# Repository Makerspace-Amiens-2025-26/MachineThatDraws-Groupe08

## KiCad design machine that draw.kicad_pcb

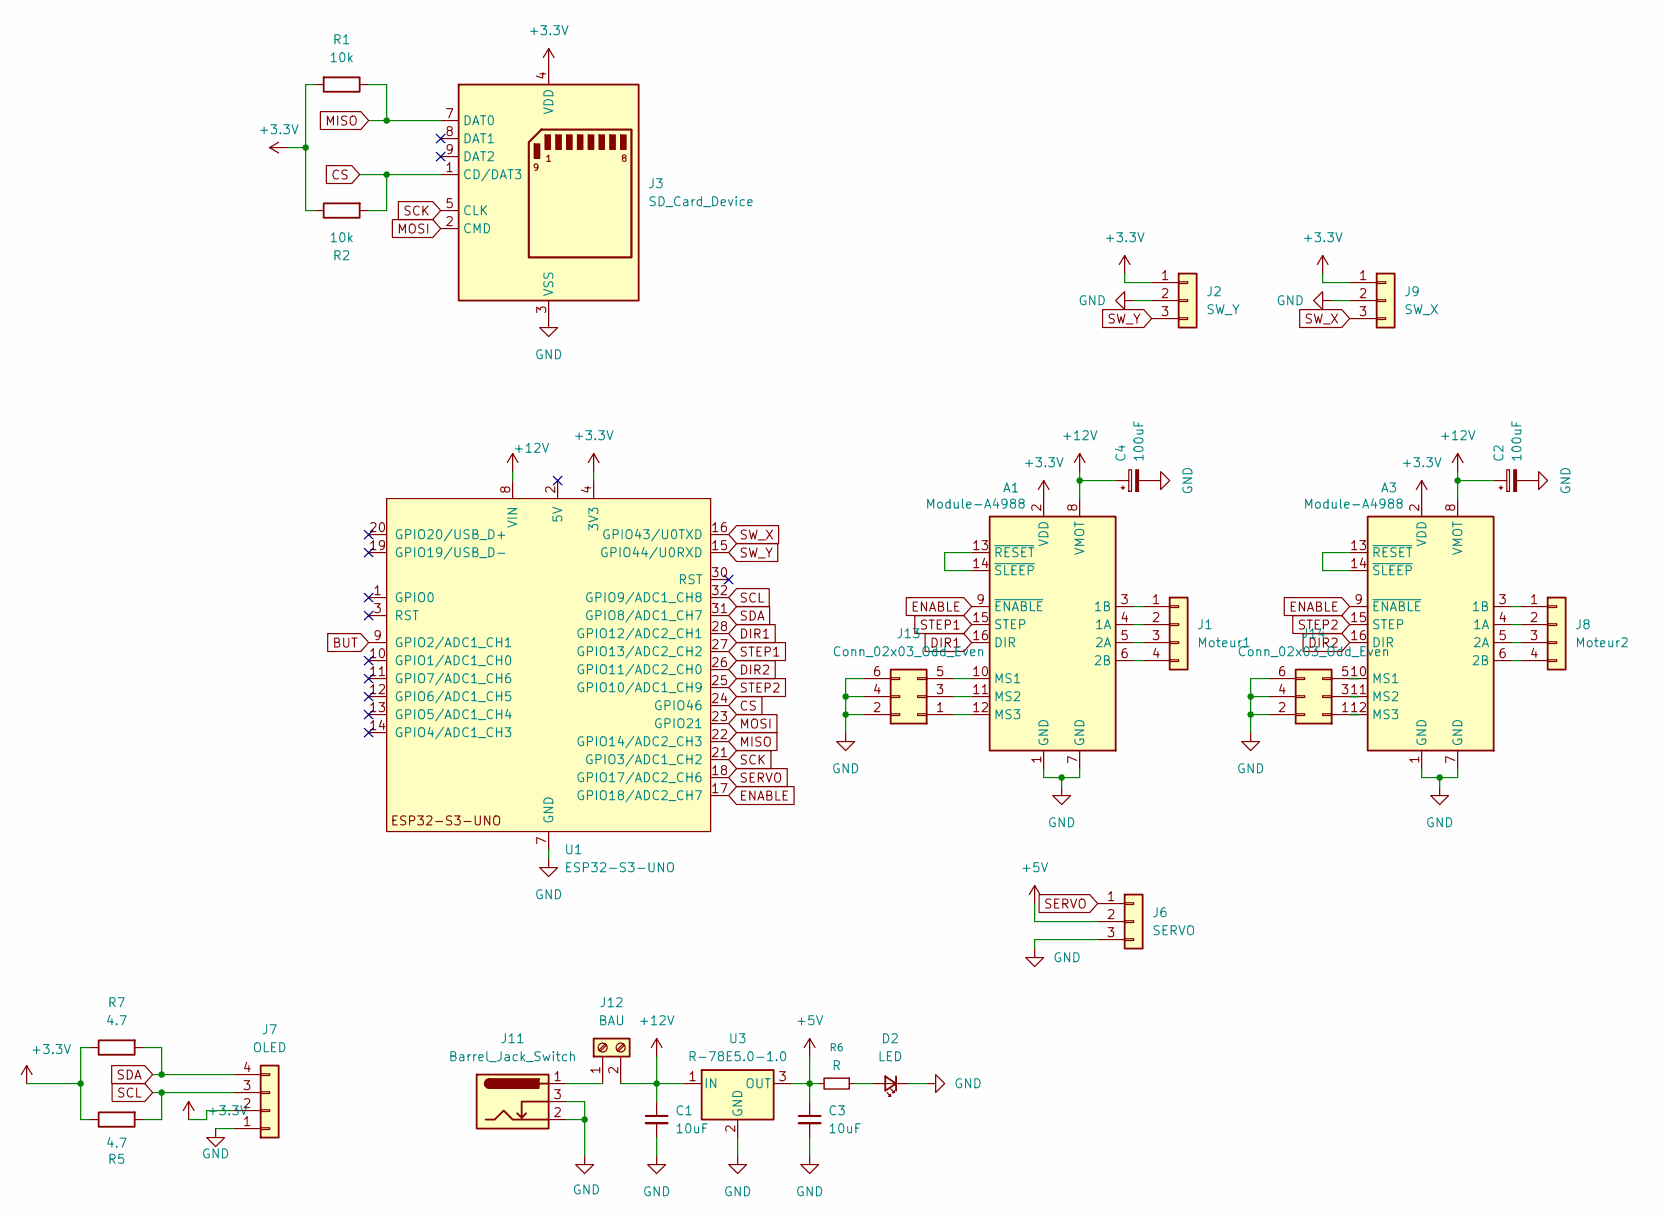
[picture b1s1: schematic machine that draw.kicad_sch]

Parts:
A1, A3: Module-A4988; Pololu_Breakout-16_15.2x20.3mm
C1, C3: 10uF; C_1206_3216Metric_Pad1.33x1.80mm_HandSolder
C2, C4: 100uF; CP_Radial_D8.0mm_P3.50mm
D2: LED; LED_1206_3216Metric_Pad1.42x1.75mm_HandSolder
J1: Moteur1; PinHeader_1x04_P2.54mm_Vertical
J2: SW_Y; PinHeader_1x03_P2.54mm_Vertical
J3: SD_Card_Device; SD_Hirose_DM1AA_SF_PEJ82
J6: SERVO; PinHeader_1x03_P2.54mm_Vertical
J7: OLED; PinHeader_1x04_P2.54mm_Vertical
J8: Moteur2; PinHeader_1x04_P2.54mm_Vertical
J9: SW_X; PinHeader_1x03_P2.54mm_Vertical
J11: Barrel_Jack_Switch; BarrelJack_Horizontal
J12: BAU; TerminalBlock_Phoenix_PT-1,5-2-5.0-H_1x02_P5.00mm_Horizontal
J13, J14: Conn_02x03_Odd_Even; PinHeader_2x03_P2.54mm_Vertical
R1, R2: 10k; R_1206
R5, R7: 4.7; R_1206
R6: R; R_1206
U1: ESP32-S3-UNO; ESP_S3_UNO
U3: R-78E5.0-1.0; Converter_DCDC_RECOM_R-78E-0.5_THT

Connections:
+3.3V: A1.2 (VDD), A3.2 (VDD), J2.1, J3.4 (VDD), J7.2, J9.1, R1.2, R2.1, R5.1, R7.1, U1.4 (3V3)
+5V: C3.1, J6.2, R6.2, U3.3 (OUT)
+12V: A1.8 (VMOT), A3.8 (VMOT), C1.1, C2.1, C4.1, J12.2, U1.8 (VIN), U3.1 (IN)
BUT: U1.9 (GPIO2/ADC1_CH1)
CS: J3.1 (CD/DAT3), R2.2, U1.24 (GPIO46)
DIR1: A1.16 (DIR), U1.28 (GPIO12/ADC2_CH1)
DIR2: A3.16 (DIR), U1.26 (GPIO11/ADC2_CH0)
ENABLE: A1.9 (~ENABLE), A3.9 (~ENABLE), U1.17 (GPIO18/ADC2_CH7)
GND: A1.1 (GND), A1.7 (GND), A3.1 (GND), A3.7 (GND), C1.2, C2.2, C3.2, C4.2, D2.1 (K), J2.2, J3.3 (VSS), J3.6 (VSS), J6.3, J7.1, J9.2, J11.2, J11.3, J13.2, J13.4, J13.6, J14.2, J14.4, J14.6, U1.6 (GND), U1.7 (GND), U1.29 (GND), U3.2 (GND)
MISO: J3.7 (DAT0), R1.1, U1.22 (GPIO14/ADC2_CH3)
MOSI: J3.2 (CMD), U1.23 (GPIO21)
unnamed: A1.4 (1A), J1.2
unnamed: A1.3 (1B), J1.1
unnamed: A1.5 (2A), J1.3
unnamed: A1.6 (2B), J1.4
unnamed: A1.10 (MS1), J13.5
unnamed: A1.11 (MS2), J13.3
unnamed: A1.12 (MS3), J13.1
unnamed: A1.13 (~RESET), A1.14 (~SLEEP)
unnamed: A3.4 (1A), J8.2
unnamed: A3.3 (1B), J8.1
unnamed: A3.5 (2A), J8.3
unnamed: A3.6 (2B), J8.4
unnamed: A3.10 (MS1), J14.5
unnamed: A3.11 (MS2), J14.3
unnamed: A3.12 (MS3), J14.1
unnamed: A3.13 (~RESET), A3.14 (~SLEEP)
unnamed: D2.2 (A), R6.1
unnamed: J11.1, J12.1
SCK: J3.5 (CLK), U1.21 (GPIO3/ADC1_CH2)
SCL: J7.3, R5.2, U1.32 (GPIO9/ADC1_CH8)
SDA: J7.4, R7.2, U1.31 (GPIO8/ADC1_CH7)
SERVO: J6.1, U1.18 (GPIO17/ADC2_CH6)
STEP1: A1.15 (STEP), U1.27 (GPIO13/ADC2_CH2)
STEP2: A3.15 (STEP), U1.25 (GPIO10/ADC1_CH9)
SW_X: J9.3, U1.16 (GPIO43/U0TXD)
SW_Y: J2.3, U1.15 (GPIO44/U0RXD)

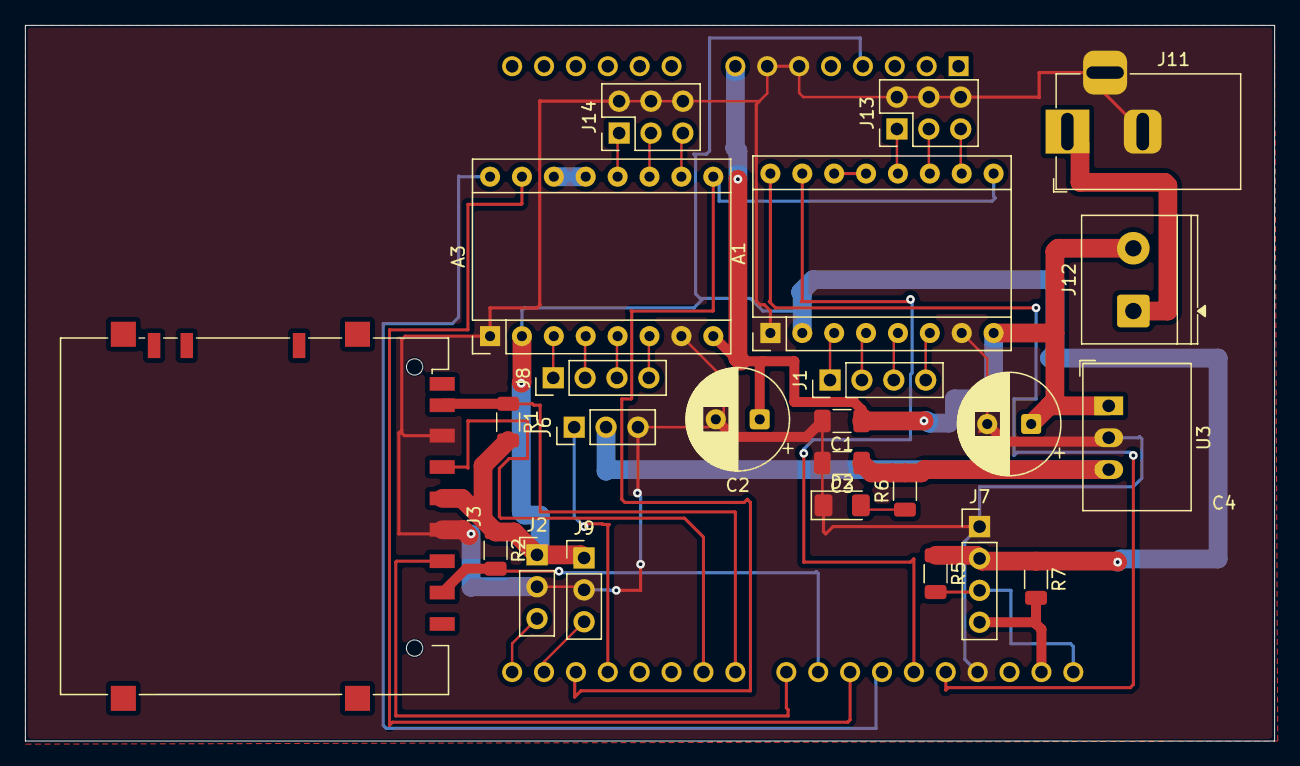
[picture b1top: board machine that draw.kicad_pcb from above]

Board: 2 copper layers, 99.5 x 57.0 mm, 25 parts (0 on the bottom side), 36 nets.

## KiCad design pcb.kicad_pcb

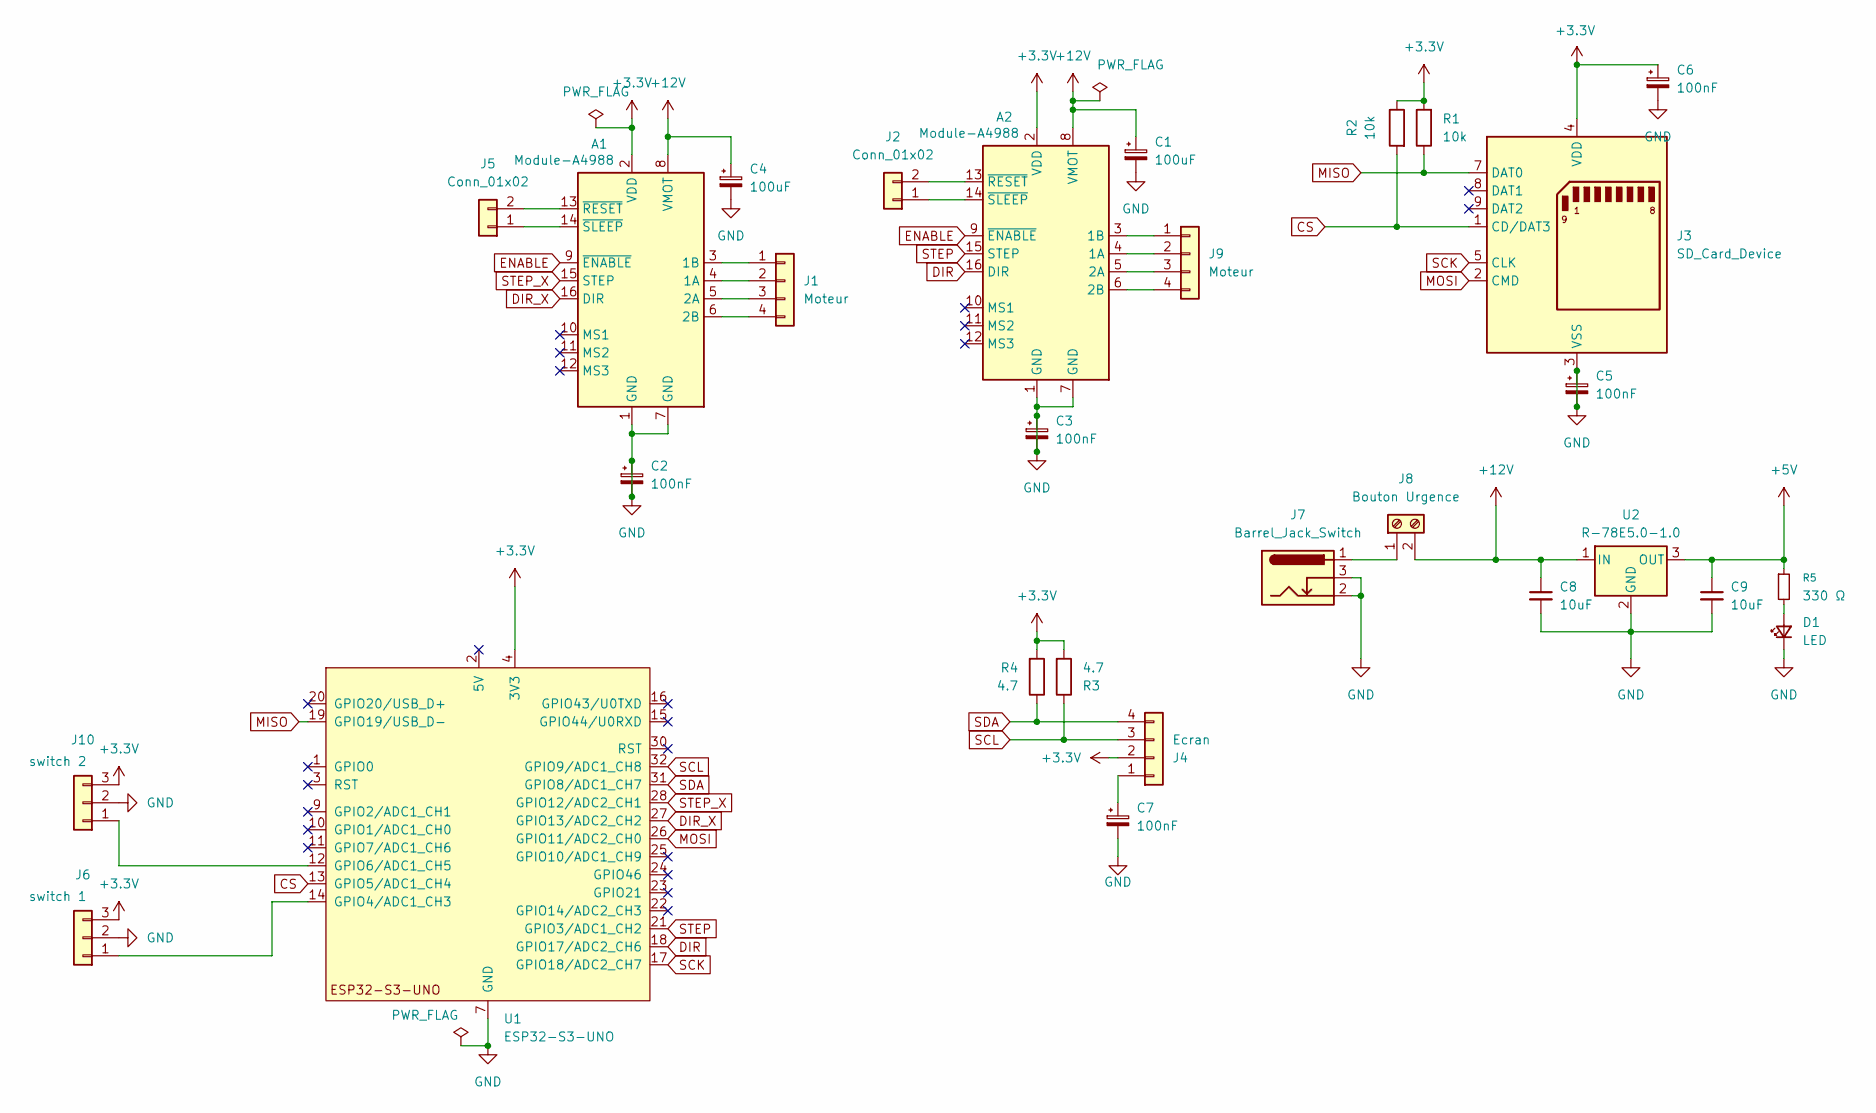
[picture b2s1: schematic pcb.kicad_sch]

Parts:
A1, A2: Module-A4988; Pololu_Breakout-16_15.2x20.3mm
C1, C4: 100uF; C_1206
C2, C3, C5, C6, C7: 100nF; C_1206
C8, C9: 10uF; C_1206_3216Metric
D1: LED; LED_1206_3216Metric
J1, J9: Moteur; PinHeader_1x04_P2.54mm_Vertical
J2, J5: Conn_01x02; PinHeader_1x02_P2.54mm_Vertical
J3: SD_Card_Device; SD_Hirose_DM1AA_SF_PEJ82
J4: Ecran; PinHeader_1x04_P2.54mm_Vertical
J6: switch 1; PinSocket_1x03_P2.54mm_Vertical
J7: Barrel_Jack_Switch; BarrelJack_Horizontal
J8: Bouton Urgence; JWT_A3963_1x02_P3.96mm_Vertical
J10: switch 2; PinSocket_1x03_P2.54mm_Vertical
R1, R2: 10k; R_Axial
R3, R4: 4.7; R_Axial
R5: 330 Ω; R_1206_3216Metric
U1: ESP32-S3-UNO; ESP_S3_UNO
U2: R-78E5.0-1.0; Converter_DCDC_RECOM_R-78E-0.5_THT

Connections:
+3.3V: A1.2 (VDD), A2.2 (VDD), C6.1, J3.4 (VDD), J4.2, J6.3, J10.3, R1.2, R2.1, R3.2, R4.2, U1.4 (3V3)
+5V: C9.1, R5.1, U2.3 (OUT)
+12V: A1.8 (VMOT), A2.8 (VMOT), C1.1, C4.1, C8.1, J8.2, U2.1 (IN)
CS: J3.1 (CD/DAT3), R2.2, U1.13 (GPIO5/ADC1_CH4)
DIR: A2.16 (DIR), U1.18 (GPIO17/ADC2_CH6)
DIR_X: A1.16 (DIR), U1.27 (GPIO13/ADC2_CH2)
ENABLE: A1.9 (~ENABLE), A2.9 (~ENABLE)
GND: A1.1 (GND), A1.7 (GND), A2.1 (GND), A2.7 (GND), C1.2, C2.1, C2.2, C3.1, C3.2, C4.2, C5.1, C5.2, C6.2, C7.2, C8.2, C9.2, D1.1 (K), J3.3 (VSS), J3.6 (VSS), J6.2, J7.2, J7.3, J10.2, U1.6 (GND), U1.7 (GND), U1.29 (GND), U2.2 (GND)
MISO: J3.7 (DAT0), R1.1, U1.19 (GPIO19/USB_D-)
MOSI: J3.2 (CMD), U1.26 (GPIO11/ADC2_CH0)
unnamed: A1.4 (1A), J1.2
unnamed: A1.3 (1B), J1.1
unnamed: A1.5 (2A), J1.3
unnamed: A1.6 (2B), J1.4
unnamed: A1.13 (~RESET), J5.2
unnamed: A1.14 (~SLEEP), J5.1
unnamed: A2.4 (1A), J9.2
unnamed: A2.3 (1B), J9.1
unnamed: A2.5 (2A), J9.3
unnamed: A2.6 (2B), J9.4
unnamed: A2.13 (~RESET), J2.2
unnamed: A2.14 (~SLEEP), J2.1
unnamed: D1.2 (A), R5.2
unnamed: C7.1, J4.1
unnamed: J6.1, U1.14 (GPIO4/ADC1_CH3)
unnamed: J7.1, J8.1
unnamed: J10.1, U1.12 (GPIO6/ADC1_CH5)
SCK: J3.5 (CLK), U1.17 (GPIO18/ADC2_CH7)
SCL: J4.3, R3.1, U1.32 (GPIO9/ADC1_CH8)
SDA: J4.4, R4.1, U1.31 (GPIO8/ADC1_CH7)
STEP: A2.15 (STEP), U1.21 (GPIO3/ADC1_CH2)
STEP_X: A1.15 (STEP), U1.28 (GPIO12/ADC2_CH1)

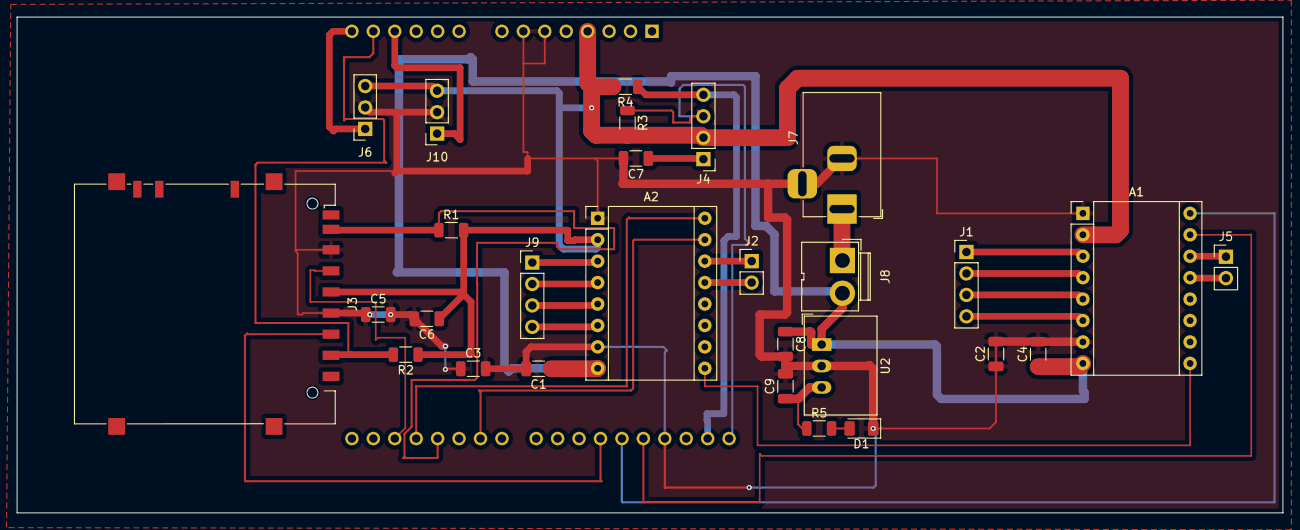
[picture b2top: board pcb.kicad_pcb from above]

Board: 2 copper layers, 150.0 x 58.8 mm, 29 parts (0 on the bottom side), 32 nets.

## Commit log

2026-04-22 Fix typo in documentation introduction
    Removed an extraneous 'hh' from the documentation.
2026-04-22 a propos du projet
    Updated project overview to provide detailed information about the Machine That Draws project, its objectives, and documentation purpose.
2026-06-05 poster
2026-06-09 vidéo
2026-06-28 conception
2026-06-28 etudes
2026-06-28 objectifs
    Updated project objectives and context, added detailed constraints and pedagogical goals.
2026-06-28 index
2026-06-28 video et assemblage
2026-06-28 index
    Updated video source and embedded iframe for Onshape model.
2026-06-28 pcb image
